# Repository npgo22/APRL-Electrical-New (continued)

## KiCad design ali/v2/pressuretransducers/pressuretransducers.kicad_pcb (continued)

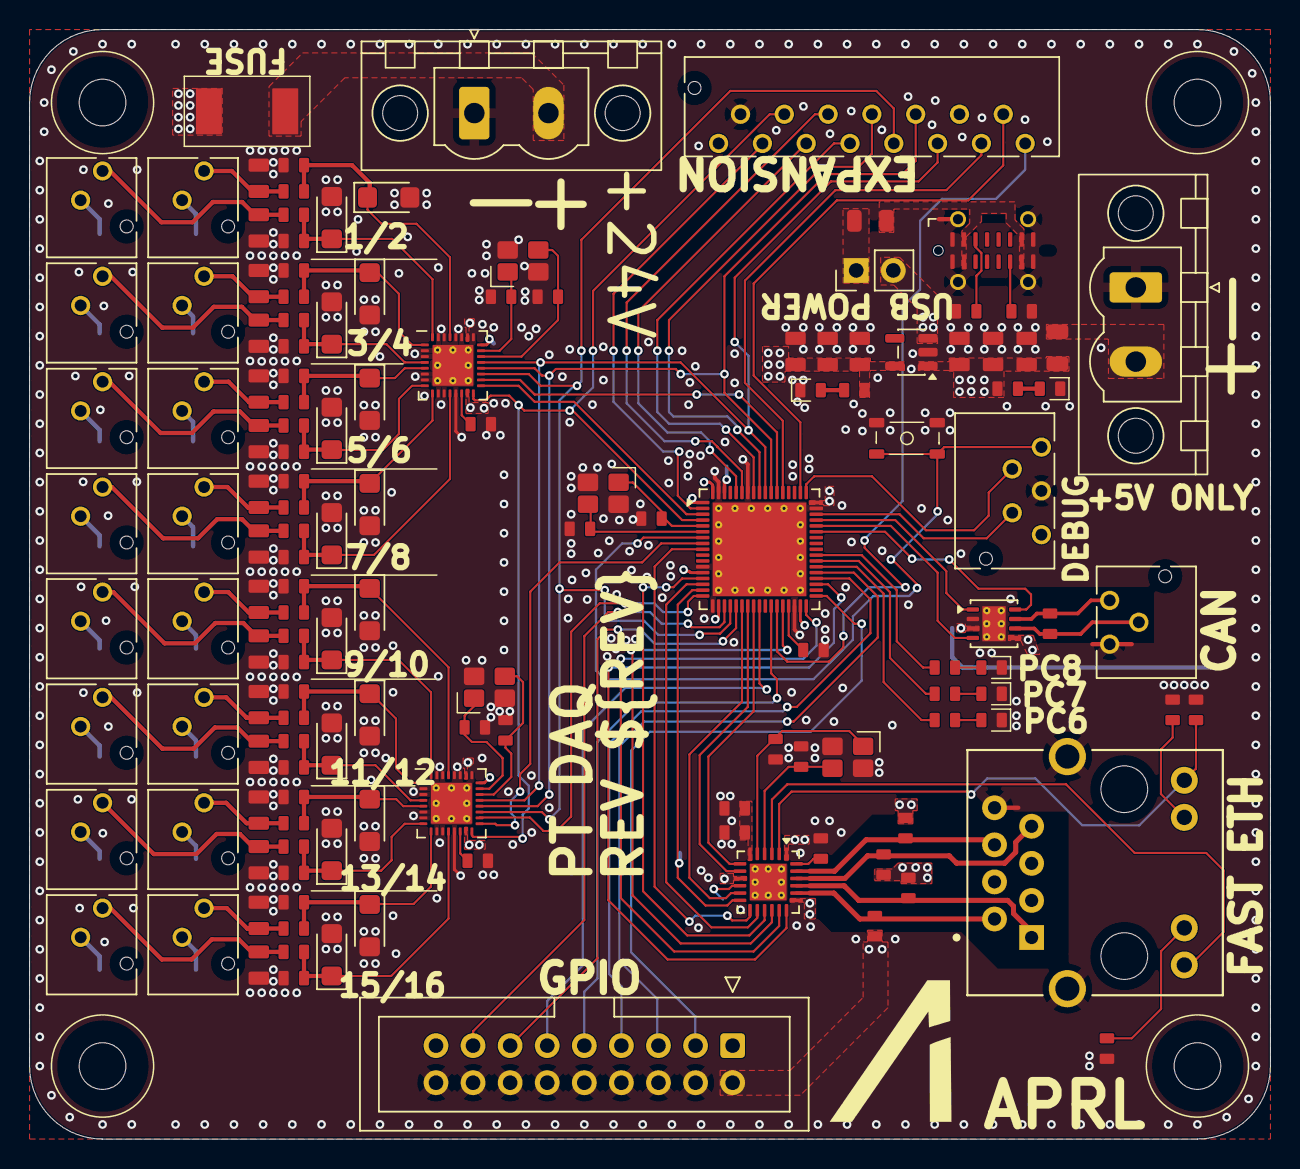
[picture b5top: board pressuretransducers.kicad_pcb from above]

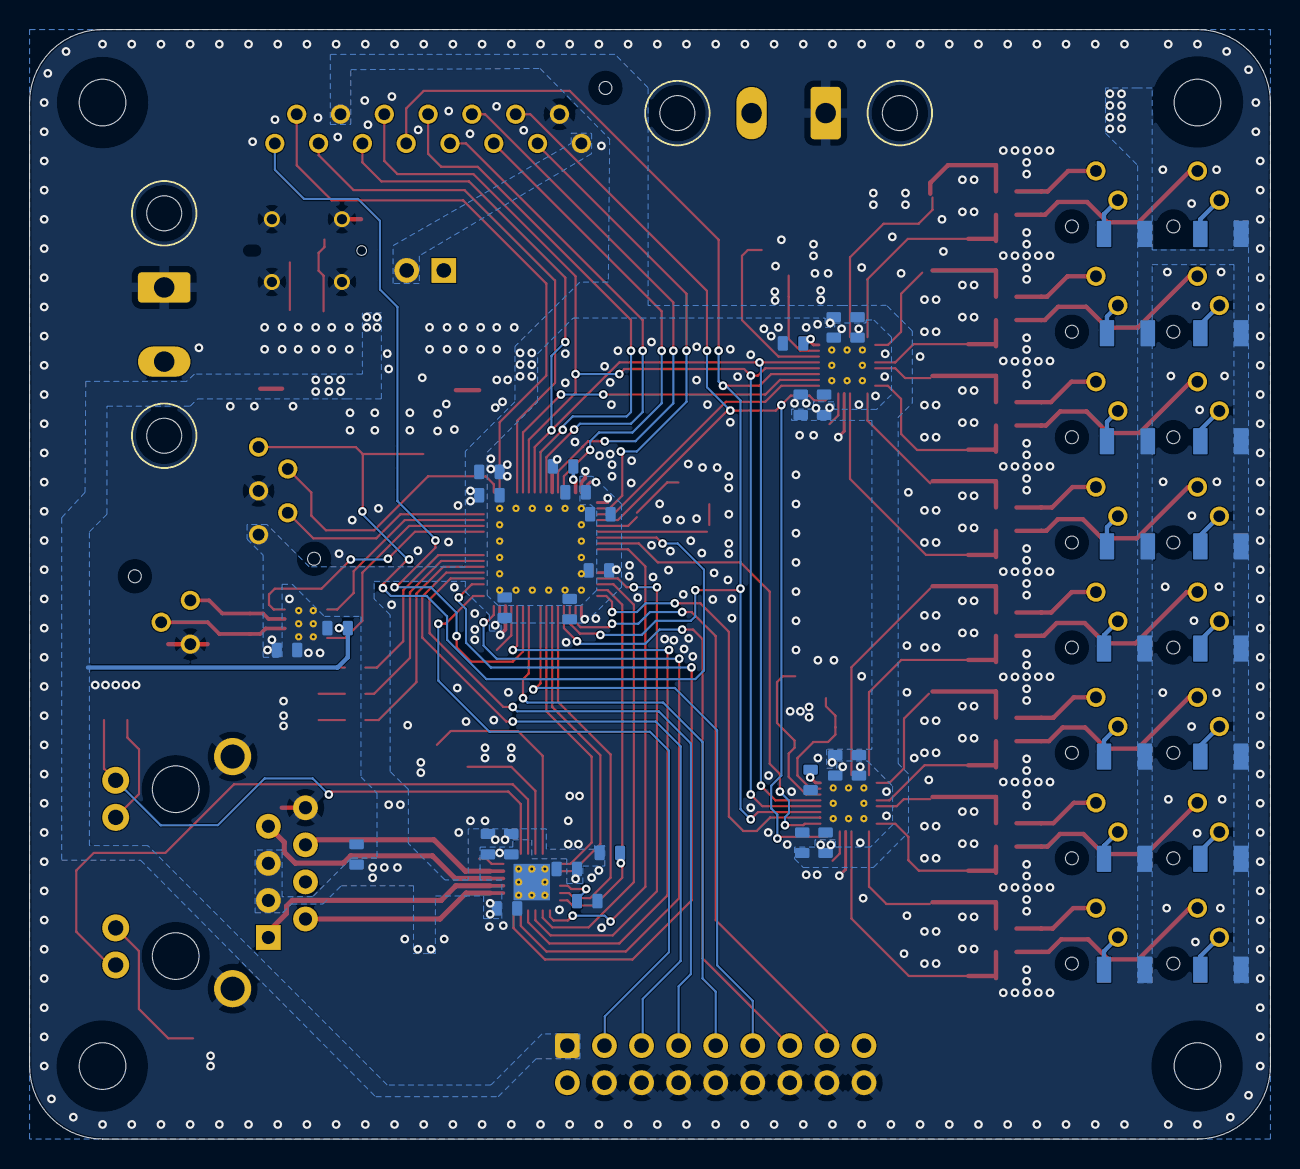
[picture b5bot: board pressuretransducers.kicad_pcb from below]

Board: 4 copper layers, 85.0 x 76.0 mm, 190 parts (43 on the bottom side), 132 nets.

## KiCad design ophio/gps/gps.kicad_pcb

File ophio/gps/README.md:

# Flight Computer / GPS (v1)

Flight computer board with GPS integration.

## KiBot

```sh
kibot -c gps.kibot.yaml
```

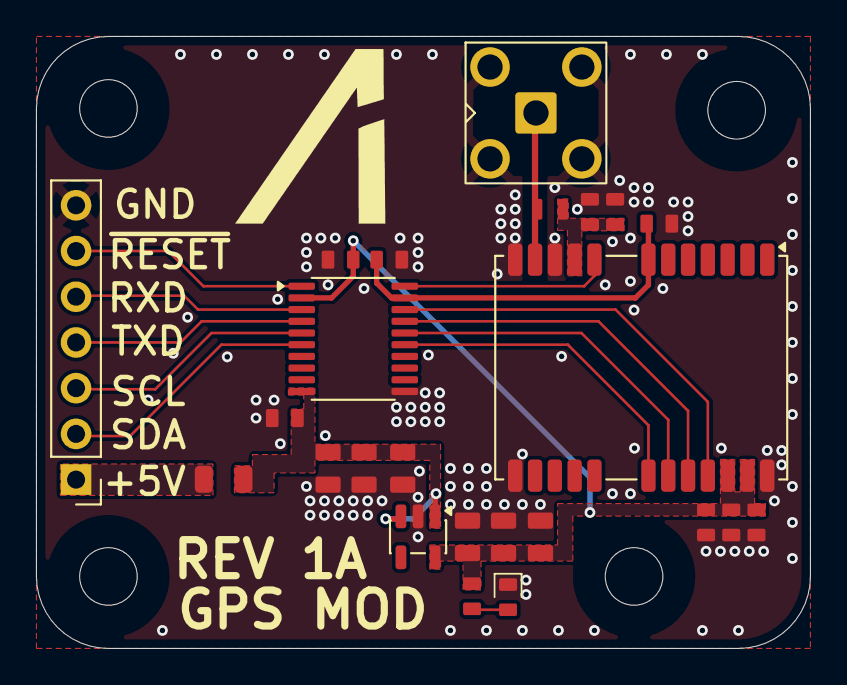
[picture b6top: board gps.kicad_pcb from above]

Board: 4 copper layers, 43.0 x 34.0 mm, 28 parts (0 on the bottom side), 18 nets.

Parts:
C1, C2, C3, C5, C7, C9: 22uF; C_0805
C4, C6, C8, C12, C14: 100nF; C_0603
C10, C11: 33pF; C_0603
C13: 100pF; C_0603
D1: LED_Small; LED_0603
F1: 100mA hold; Fuse_0805_2012Metric
H1, H2, H3, H4: MountingHole; MountingHole_3.2mm_M3
J1: Conn_01x07; PinHeader_1x07_P2.54mm_Vertical
J2: SMA; SMA_BAT_Wireless_BWSMA-KWE-Z001
L1: 68 nH; LQW18AN68NG8Z
R1, R2: 10k; R_0603
U1: AP2112K-3.3; SOT-23-5
U2: TXS0108EPW; TSSOP-20_4.4x6.5mm_P0.65mm
U3: LC29H; ublox_NEO

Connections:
+2.8V: C6.1, C12.1, U2.19 (VCCB), U3.7 (VDD_EXT)
+3.3V: C4.1, C5.1, C7.1, C8.1, C9.1, C10.1, C11.1, R2.1, U1.5 (VOUT), U2.2 (VCCA), U3.22 (V_BCKP), U3.23 (VCC)
+5V: C1.1, C2.1, C3.1, F1.1, R1.1, U1.1 (VIN), U1.3 (EN), U2.10 (OE)
/I2C_SCL: U2.16 (B4), U3.19 (I2C_SCL)
/I2C_SDA: U2.15 (B5), U3.18 (I2C_SDA)
/RXD: U2.18 (B2), U3.21 (RXD)
/TXD: U2.17 (B3), U3.20 (TXD)
/~RESET: U2.20 (B1), U3.8 (~RESET)
GND: C1.2, C2.2, C3.2, C4.2, C5.2, C6.2, C7.2, C8.2, C9.2, C10.2, C11.2, C12.2, C13.2, C14.2, D1.1 (K), J1.7, J2.2 (Ext), R1.2, U1.2 (GND), U2.11 (GND), U3.10 (GND), U3.12 (GND), U3.13 (GND), U3.24 (GND)
unnamed: D1.2 (A), R2.2
unnamed: F1.2, J1.1
unnamed: J1.2, U2.6 (A5)
unnamed: J1.3, U2.5 (A4)
unnamed: J1.4, U2.4 (A3)
unnamed: J1.5, U2.3 (A2)
unnamed: J1.6, U2.1 (A1)
unnamed: J2.1 (In), L1.2, U3.11 (RF_IN)
unnamed: C13.1, C14.1, L1.1, U3.9 (VDD_RF)

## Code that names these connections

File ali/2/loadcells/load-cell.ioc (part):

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Mcu.Name=STM32H563RIVx
Mcu.Package=VFQFPN68
Mcu.UserName=STM32H563RIVx
PA0.GPIOParameters=GPIO_Label
PA0.GPIO_Label=ETH_nRST
PA0.Signal=GPIO_Output
PA1.GPIOParameters=GPIO_Label
PA1.GPIO_Label=ETH_REF_CLK
PA1.Mode=RMII
PA1.Signal=ETH_REF_CLK
PA10.GPIOParameters=GPIO_Label
PA10.GPIO_Label=FDCAN_STDBY
PA10.Signal=GPIO_Output
PA11.GPIOParameters=GPIO_Label
PA11.GPIO_Label=FDCAN_RX
PA11.Mode=FDCAN_Activate
PA11.Signal=FDCAN1_RX
PA12.GPIOParameters=GPIO_Label
PA12.GPIO_Label=FDCAN_TX
PA12.Mode=FDCAN_Activate
PA12.Signal=FDCAN1_TX
PA13(JTMS/SWDIO).GPIOParameters=GPIO_Label
PA13(JTMS/SWDIO).GPIO_Label=SWDIO
PA13(JTMS/SWDIO).Mode=Serial_Wire
PA13(JTMS/SWDIO).Signal=DEBUG_JTMS-SWDIO
PA14(JTCK/SWCLK).GPIOParameters=GPIO_Label
PA14(JTCK/SWCLK).GPIO_Label=SWCLK
PA14(JTCK/SWCLK).Mode=Serial_Wire
PA14(JTCK/SWCLK).Signal=DEBUG_JTCK-SWCLK
PA15(JTDI).GPIOParameters=GPIO_Label
PA15(JTDI).GPIO_Label=TIM2_CH1
PA15(JTDI).Signal=S_TIM2_CH1
PA2.GPIOParameters=GPIO_Label
PA2.GPIO_Label=ETH_MDIO
PA2.Mode=RMII
PA2.Signal=ETH_MDIO
PA3.GPIOParameters=GPIO_Label
PA3.GPIO_Label=TIM2_CH4
PA3.Signal=S_TIM2_CH4
PA4.Signal=GPIO_Output
PA5.GPIOParameters=GPIO_Label
PA5.GPIO_Label=ADC_SCLK
PA5.Mode=Full_Duplex_Master
PA5.Signal=SPI1_SCK
PA6.Signal=GPIO_Output
PA7.GPIOParameters=GPIO_Label
PA7.GPIO_Label=ETH_CRS_DV
PA7.Mode=RMII
PA7.Signal=ETH_CRS_DV
PB0.Signal=GPIO_Output
PB1.GPIOParameters=GPIO_Label
PB1.GPIO_Label=SENSE_+5V
PB1.Signal=ADCx_INP5
PB10.GPIOParameters=GPIO_Label
PB10.GPIO_Label=TIM2_CH3
PB10.Signal=S_TIM2_CH3
PB11.GPIOParameters=GPIO_Label
PB11.GPIO_Label=ETH_TX_EN
PB11.Mode=RMII
PB11.Signal=ETH_TX_EN
PB12.GPIOParameters=GPIO_Label
PB12.GPIO_Label=ETH_TXD0
PB12.Mode=RMII
PB12.Signal=ETH_TXD0
PB13.Signal=GPIO_Output
PB14.Signal=GPIO_Output
PB15.GPIOParameters=GPIO_Label
PB15.GPIO_Label=ETH_TXD1
PB15.Mode=RMII
PB15.Signal=ETH_TXD1
PB2.Signal=GPIO_Output
PB3(JTDO/TRACESWO).GPIOParameters=GPIO_Label
PB3(JTDO/TRACESWO).GPIO_Label=ADC_DRDY
PB3(JTDO/TRACESWO).Signal=S_TIM2_CH2
PB4(NJTRST).GPIOParameters=GPIO_Label
PB4(NJTRST).GPIO_Label=ADC_MISO
PB4(NJTRST).Mode=Full_Duplex_Master
PB4(NJTRST).Signal=SPI1_MISO
PB5.GPIOParameters=GPIO_Label
PB5.GPIO_Label=ADC_MOSI
PB5.Mode=Full_Duplex_Master
PB5.Signal=SPI1_MOSI
PB6.GPIOParameters=GPIO_Label
PB6.GPIO_Label=I2C1_SCL
PB6.Mode=I2C
PB6.Signal=I2C1_SCL
PB7.GPIOParameters=GPIO_Label
PB7.GPIO_Label=I2C1_SCA
PB7.Mode=I2C
PB7.Signal=I2C1_SDA
PB8.GPIOParameters=GPIO_Label
PB8.GPIO_Label=UART4_RX
PB8.Mode=Asynchronous
PB8.Signal=UART4_RX
PB9.GPIOParameters=GPIO_Label
PB9.GPIO_Label=UART4_TX
PB9.Mode=Asynchronous
PB9.Signal=UART4_TX
PC0.GPIOParameters=GPIO_Label
PC0.GPIO_Label=ADC2_CS
PC0.Signal=GPIO_Output
PC1.GPIOParameters=GPIO_Label
PC1.GPIO_Label=ETH_MDC
PC1.Mode=RMII
PC1.Signal=ETH_MDC
PC12.Signal=GPIO_Output
PC13.GPIOParameters=GPIO_Label
PC13.GPIO_Label=ADC1_CS
PC13.Signal=GPIO_Output
PC14-OSC32_IN(OSC32_IN).GPIOParameters=GPIO_Label
PC14-OSC32_IN(OSC32_IN).GPIO_Label=ADC_START
PC14-OSC32_IN(OSC32_IN).Signal=GPIO_Output
PC15-OSC32_OUT(OSC32_OUT).GPIOParameters=GPIO_Label
PC15-OSC32_OUT(OSC32_OUT).GPIO_Label=ADC_RESET
PC15-OSC32_OUT(OSC32_OUT).Signal=GPIO_Output
PC2.GPIOParameters=GPIO_Label
PC2.GPIO_Label=ADC3_CS
PC2.Signal=GPIO_Output
PC3.GPIOParameters=GPIO_Label
PC3.GPIO_Label=ADC4_CS
PC3.Signal=GPIO_Output
PC4.GPIOParameters=GPIO_Label
PC4.GPIO_Label=ETH_RXD0
PC4.Mode=RMII
PC4.Signal=ETH_RXD0
PC5.GPIOParameters=GPIO_Label
PC5.GPIO_Label=ETH_RXD1
PC5.Mode=RMII
PC5.Signal=ETH_RXD1
PC6.GPIOParameters=GPIO_Label
PC6.GPIO_Label=USER_LED_2
PC6.Signal=GPIO_Output
PC7.GPIOParameters=GPIO_Label
PC7.GPIO_Label=USER_LED_3
PC7.Signal=GPIO_Output
PD11.Signal=GPIO_Output
PD12.GPIOParameters=GPIO_Label
PD12.GPIO_Label=USER_LED_1
PD12.Signal=GPIO_Output
PH0-OSC_IN(PH0).Mode=HSE-External-Oscillator
PH0-OSC_IN(PH0).Signal=RCC_OSC_IN
PH1-OSC_OUT(PH1).Mode=HSE-External-Oscillator
PH1-OSC_OUT(PH1).Signal=RCC_OSC_OUT
RCC.HSE_VALUE=25000000
RCC.SYSCLKFreq_VALUE=32000000
board=custom

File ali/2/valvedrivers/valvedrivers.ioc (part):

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Mcu.Name=STM32H563RIVx
Mcu.Package=VFQFPN68
Mcu.UserName=STM32H563RIVx
PA0.GPIOParameters=GPIO_Label
PA0.GPIO_Label=ETH_nRST
PA0.Signal=GPIO_Output
PA1.Mode=RMII
PA1.Signal=ETH_REF_CLK
PA10.GPIOParameters=GPIO_Label
PA10.GPIO_Label=FDCAN_STDBY
PA10.Signal=GPIO_Output
PA11.Mode=FDCAN_Activate
PA11.Signal=FDCAN1_RX
PA12.Mode=FDCAN_Activate
PA12.Signal=FDCAN1_TX
PA13(JTMS/SWDIO).Mode=Serial_Wire
PA13(JTMS/SWDIO).Signal=DEBUG_JTMS-SWDIO
PA14(JTCK/SWCLK).Mode=Serial_Wire
PA14(JTCK/SWCLK).Signal=DEBUG_JTCK-SWCLK
PA2.Mode=RMII
PA2.Signal=ETH_MDIO
PA3.GPIOParameters=GPIO_Label
PA3.GPIO_Label=DRV2_4_STAT
PA3.Signal=GPIO_Input
PA4.GPIOParameters=GPIO_Label
PA4.GPIO_Label=DRV3_1_IN
PA4.Signal=GPIO_Output
PA5.GPIOParameters=GPIO_Label
PA5.GPIO_Label=DRV3_2_IN
PA5.Signal=GPIO_Output
PA6.GPIOParameters=GPIO_Label
PA6.GPIO_Label=DRV3_3_IN
PA6.Signal=GPIO_Output
PA7.Mode=RMII
PA7.Signal=ETH_CRS_DV
PA8.GPIOParameters=GPIO_Label
PA8.GPIO_Label=nBRK_STAT
PA8.Signal=GPIO_Input
PA9.GPIOParameters=GPIO_Label
PA9.GPIO_Label=nBUSS_EN
PA9.Signal=GPIO_Input
PB0.GPIOParameters=GPIO_Label
PB0.GPIO_Label=DRV3_4_IN
PB0.Signal=GPIO_Output
PB1.GPIOParameters=GPIO_Label
PB1.GPIO_Label=DRV3_1_STAT
PB1.Signal=GPIO_Input
PB10.GPIOParameters=GPIO_Label
PB10.GPIO_Label=DRV3_3_STAT
PB10.Signal=GPIO_Input
PB11.Mode=RMII
PB11.Signal=ETH_TX_EN
PB12.Mode=RMII
PB12.Signal=ETH_TXD0
PB13.GPIOParameters=GPIO_Label
PB13.GPIO_Label=DRV3_4_STAT
PB13.Signal=GPIO_Input
PB15.Mode=RMII
PB15.Signal=ETH_TXD1
PB2.GPIOParameters=GPIO_Label
PB2.GPIO_Label=DRV3_2_STAT
PB2.Signal=GPIO_Input
PB3(JTDO/TRACESWO).GPIOParameters=GPIO_Label
PB3(JTDO/TRACESWO).GPIO_Label=DRV1_3_IN
PB3(JTDO/TRACESWO).Signal=GPIO_Output
PB4(NJTRST).GPIOParameters=GPIO_Label
PB4(NJTRST).GPIO_Label=DRV1_4_IN
PB4(NJTRST).Signal=GPIO_Output
PB5.GPIOParameters=GPIO_Label
PB5.GPIO_Label=DRV2_1_IN
PB5.Signal=GPIO_Output
PB6.GPIOParameters=GPIO_Label
PB6.GPIO_Label=DRV2_2_IN
PB6.Signal=GPIO_Output
PB7.GPIOParameters=GPIO_Label
PB7.GPIO_Label=DRV2_3_IN
PB7.Signal=GPIO_Output
PB8.GPIOParameters=GPIO_Label
PB8.GPIO_Label=DRV2_4_IN
PB8.Signal=GPIO_Output
PB9.GPIOParameters=GPIO_Label
PB9.GPIO_Label=DRV1_1_STAT
PB9.Signal=GPIO_Input
PC0.GPIOParameters=GPIO_Label
PC0.GPIO_Label=DRV2_1_STAT
PC0.Signal=GPIO_Input
PC1.Mode=RMII
PC1.Signal=ETH_MDC
PC11.GPIOParameters=GPIO_Label
PC11.GPIO_Label=DRV1_1_IN
PC11.Signal=GPIO_Output
PC12.GPIOParameters=GPIO_Label
PC12.GPIO_Label=DRV1_2_IN
PC12.Signal=GPIO_Output
PC13.GPIOParameters=GPIO_Label
PC13.GPIO_Label=DRV1_2_STAT
PC13.Signal=GPIO_Input
PC14-OSC32_IN(OSC32_IN).GPIOParameters=GPIO_Label
PC14-OSC32_IN(OSC32_IN).GPIO_Label=DRV1_3_STAT
PC14-OSC32_IN(OSC32_IN).Signal=GPIO_Input
PC15-OSC32_OUT(OSC32_OUT).GPIOParameters=GPIO_Label
PC15-OSC32_OUT(OSC32_OUT).GPIO_Label=DRV1_4_STAT
PC15-OSC32_OUT(OSC32_OUT).Signal=GPIO_Input
PC2.GPIOParameters=GPIO_Label
PC2.GPIO_Label=DRV2_2_STAT
PC2.Signal=GPIO_Input
PC3.GPIOParameters=GPIO_Label
PC3.GPIO_Label=DRV2_3_STAT
PC3.Signal=GPIO_Input
PC4.Mode=RMII
PC4.Signal=ETH_RXD0
PC5.Mode=RMII
PC5.Signal=ETH_RXD1
PC6.GPIOParameters=GPIO_Label
PC6.GPIO_Label=USER_LED_1
PC6.Signal=GPIO_Output
PC7.GPIOParameters=GPIO_Label
PC7.GPIO_Label=USER_LED_2
PC7.Signal=GPIO_Output
PC8.GPIOParameters=GPIO_Label
PC8.GPIO_Label=USER_LED_3
PC8.Signal=GPIO_Output
PC9.GPIOParameters=GPIO_Label
PC9.GPIO_Label=IGNIG
PC9.Signal=GPIO_Output
PH0-OSC_IN(PH0).Mode=HSE-External-Oscillator
PH0-OSC_IN(PH0).Signal=RCC_OSC_IN
PH1-OSC_OUT(PH1).Mode=HSE-External-Oscillator
PH1-OSC_OUT(PH1).Signal=RCC_OSC_OUT
RCC.HSE_VALUE=25000000
RCC.SYSCLKFreq_VALUE=250000000
RCC.SYSCLKSource=RCC_SYSCLKSOURCE_PLLCLK
board=custom
